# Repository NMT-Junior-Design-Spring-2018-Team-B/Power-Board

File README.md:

Power Board
===========

Repository of board design files for the possible power distribution board.

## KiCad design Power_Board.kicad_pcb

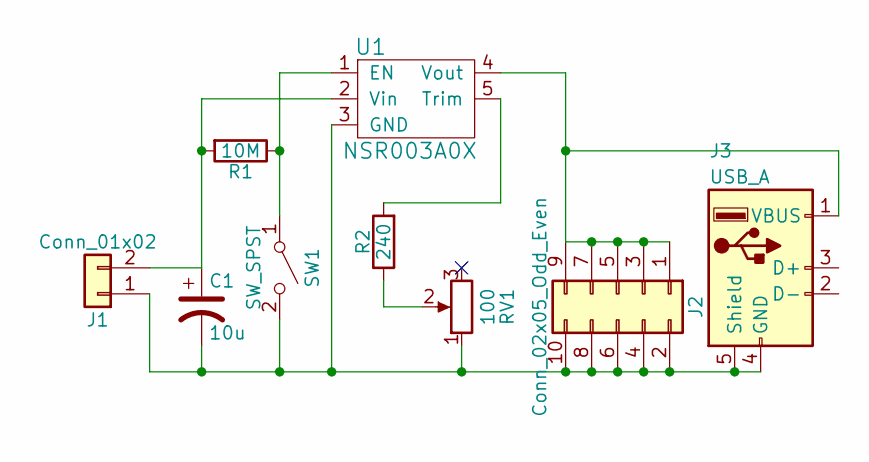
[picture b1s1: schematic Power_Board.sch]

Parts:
C1: 10u
J1: Conn_01x02
J2: Conn_02x05_Odd_Even
J3: USB_A
R1: 10M
R2: 240
RV1: 100
SW1: SW_SPST
U1: NSR003A0X

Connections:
unnamed: C1.1, J1.2, R1.2, U1.2 (Vin)
unnamed: C1.2, J1.1, J2.2, J2.4, J2.6, J2.8, J2.10, J3.4 (GND), J3.5 (Shield), RV1.1, SW1.2 (B), U1.3 (GND)
unnamed: J2.1, J2.3, J2.5, J2.7, J2.9, J3.1 (VBUS), U1.4 (Vout)
unnamed: R1.1, SW1.1 (A), U1.1 (EN)
unnamed: R2.1, RV1.2
unnamed: R2.2, U1.5 (Trim)

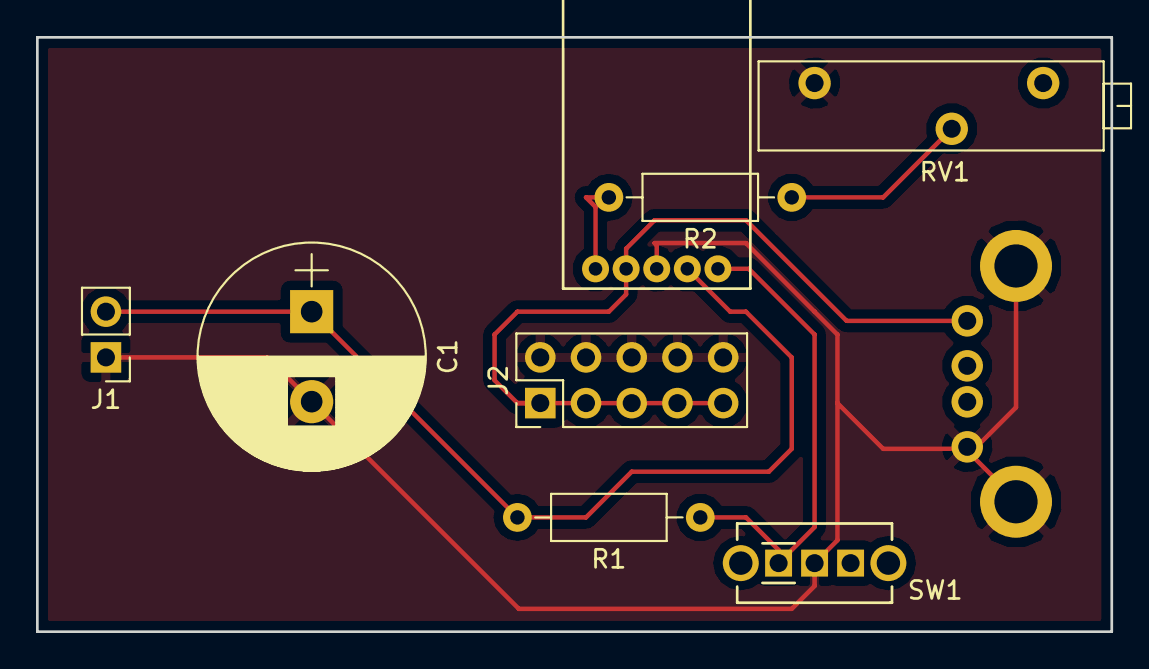
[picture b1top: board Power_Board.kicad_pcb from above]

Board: 2 copper layers, 59.7 x 33.0 mm, 9 parts (1 on the bottom side), 6 nets.

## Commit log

2018-02-22 Initial Commit - added gitignore, Readme
2018-02-22 Added revision 1 of the schematic
2018-02-22 Updated design, shrunk more
2018-02-22 Updated design, added backplane
2018-03-06 Updated to version 2, corrected footprints
2018-03-20 Moved location for board, attempting production v1
2018-03-20 modified gitignore
